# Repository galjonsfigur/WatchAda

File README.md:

# Ada-powereded digital watch

This repository contains Schematics, KiCad design files and software for Ada-powereded digital watch.
It uses wonderful work of [msp430-ada project](https://sourceforge.net/projects/msp430ada/) by Brian Drummond.
Software for this watch is a modification of original project and adds missing
features like automatic brightness, temperature reading and Easter Egg.

Revision 1 of the PCB was tested and following problems have been found:

- Incorrect footprint of CR2032 Battery holder
- THT Crystal footprint is too big and will be replaced with Epson MC-146 32kHz Crystal

Revision 2 fixed those problems and after about year of testing it haven't showed other flaws.
More photos and renders can be found in `photos` folder.

GCC compiler for building this project can be found in this repository. It was built on CentOS 6 x64 and should work with any modern 64-bit GNU/Linux distribution.
Docker image for it is still in progress as it requires exact same version of host GCC and patches from MSP430-Ada project.

## BOM and assembly instructions
Interactive BOM can be found [here](hardware/rev2/bom/ibom.html).

Remember to start with SMD components. Program the MSP430, put the display in place and
test it before soldering it to the board.

Case can be 3D printed with semi-transparent material or cut from thin PMMA.

The best way to program the microcontroller is to use [SOICBite](https://github.com/SimonMerrett/SOICbite) connected
to MSP430-G2 Launchpad. Pin layout can be found in the schematic and only TEST, RST, GND and 3V need to be used to program it.
After connecting the SOICBite, `make flash` command can be used. It uses `mspdebug` program and works only on GNU/Linux environment.
The firmware binary can be found in `firmware/obj` folder.

# License
GPL (Same as MSP430-Ada project)

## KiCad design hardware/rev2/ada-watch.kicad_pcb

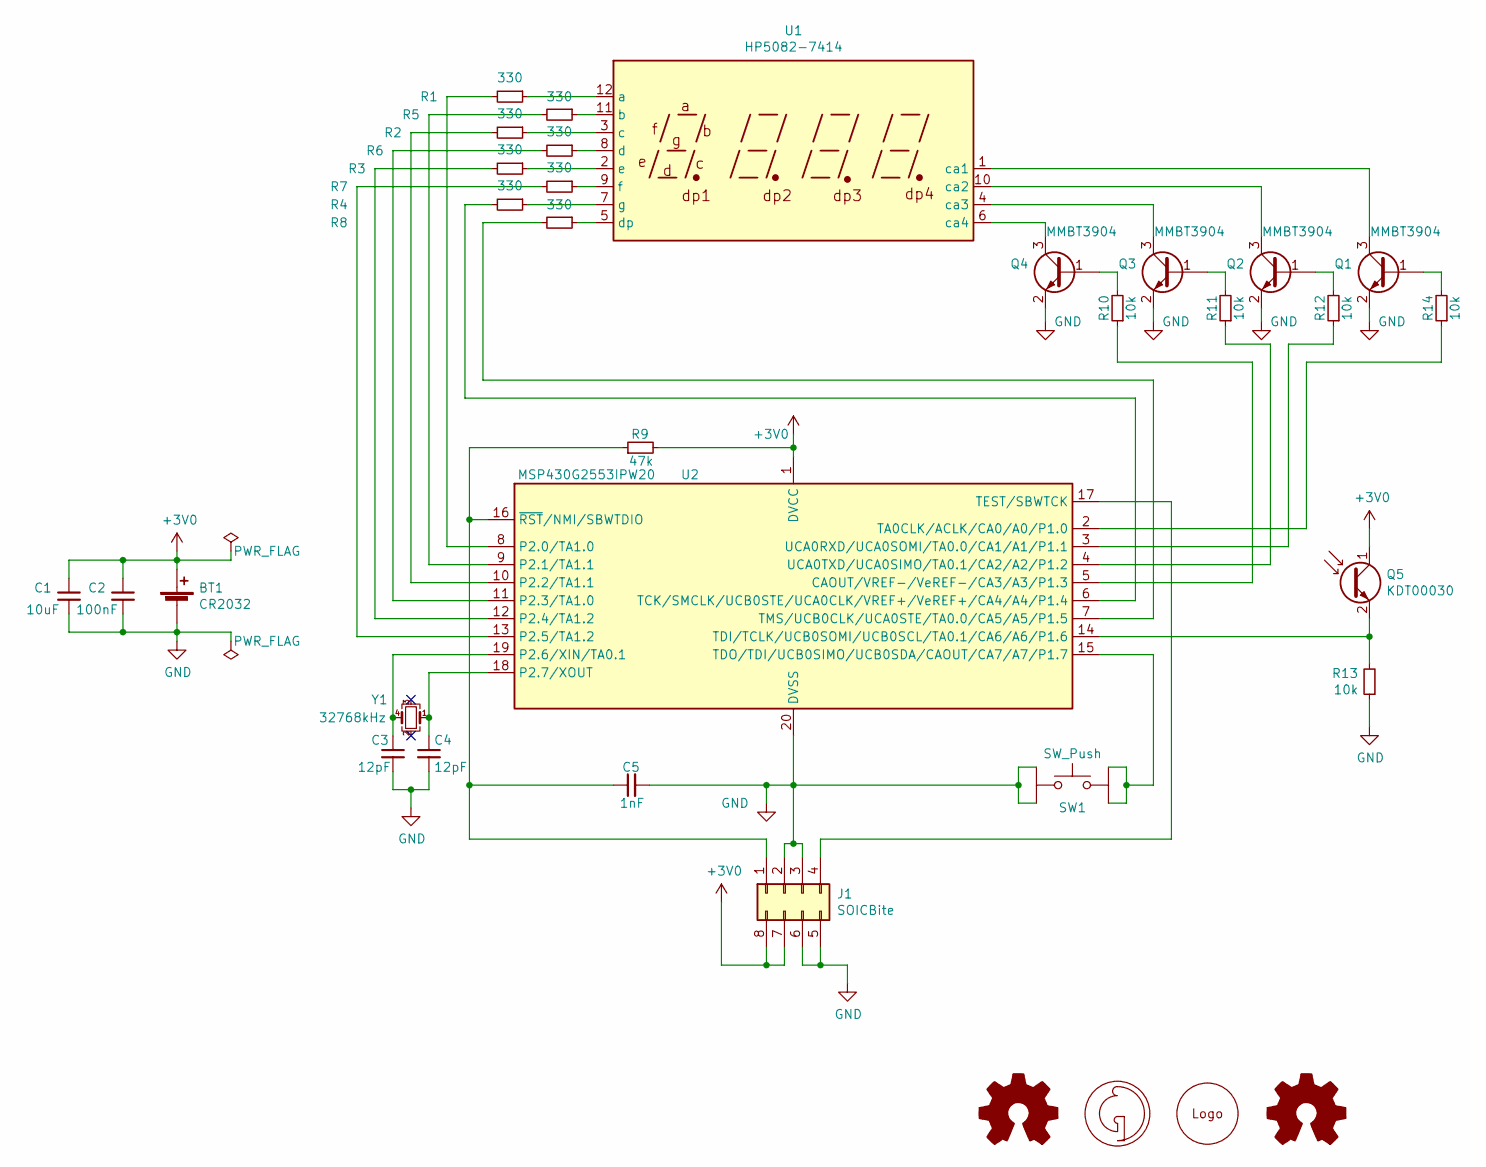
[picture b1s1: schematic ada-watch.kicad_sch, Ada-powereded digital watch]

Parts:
BT1: CR2032; BatteryHolder_Pinrex_780-72-00GF51_1x2032_customSilk
C1: 10uF; C_0805_2012Metric
C2: 100nF; C_0805_2012Metric
C3, C4: 12pF; C_0402_1005Metric
C5: 1nF; C_0402_1005Metric
J1: SOICBite; SOIC_clipProgSmall
LG1: Ada_Logo_Small
LG2: Galion_Logo; Galion_Logo_Small
LG3: Logo_Open_Hardware_Small; OSHW-Logo_5.7x6mm_SilkScreen
LG4: Logo_Designed_With_KiCad; KiCad-Logo_6mm_SilkScreen
Q1, Q2, Q3, Q4: MMBT3904; SOT-23
Q5: KDT00030; LED_0603_1608Metric
R1, R2, R3, R4, R5, R6, R7, R8: 330; R_0603_1608Metric_Pad1.05x0.95mm_HandSolder
R9: 47k; R_0603_1608Metric
R10, R11, R12, R13, R14: 10k; R_0603_1608Metric_Pad1.05x0.95mm_HandSolder
SW1: SW_Push; SKRPACE010
U1: HP5082-7414; DIP-12_W7.62mm_CustomPads_NoSilk
U2: MSP430G2553IPW20; TSSOP-20_4.4x6.5mm_P0.65mm
Y1: 32768kHz; Crystal_SMD_SeikoEpson_MC146-4Pin_6.7x1.5mm_HandSoldering

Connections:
+3V0: BT1.1 (+), C1.1, C2.1, J1.7, J1.8, Q5.1 (C), R9.2, U2.1 (DVCC)
GND: BT1.2 (-), C1.2, C2.2, C3.2, C4.2, C5.2, J1.2, J1.3, J1.5, J1.6, Q1.2 (E), Q2.2 (E), Q3.2 (E), Q4.2 (E), R13.1, SW1.3, SW1.4, U2.20 (DVSS)
unnamed: C3.1, U2.19 (P2.6/XIN/TA0.1), Y1.4
unnamed: C4.1, U2.18 (P2.7/XOUT), Y1.1
unnamed: C5.1, J1.1, R9.1, U2.16 (~RST~/NMI/SBWTDIO)
unnamed: J1.4, U2.17 (TEST/SBWTCK)
unnamed: Q1.1 (B), R14.2
unnamed: Q1.3 (C), U1.1 (ca1)
unnamed: Q2.1 (B), R12.2
unnamed: Q2.3 (C), U1.10 (ca2)
unnamed: Q3.1 (B), R11.2
unnamed: Q3.3 (C), U1.4 (ca3)
unnamed: Q4.1 (B), R10.2
unnamed: Q4.3 (C), U1.6 (ca4)
unnamed: Q5.2 (E), R13.2, U2.14 (TDI/TCLK/UCB0SOMI/UCB0SCL/TA0.1/CA6/A6/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)
unnamed: R1.1, U1.12 (a)
unnamed: R1.2, U2.8 (P2.0/TA1.0)
unnamed: R2.1, U1.3 (c)
unnamed: R2.2, U2.10 (P2.2/TA1.1)
unnamed: R3.1, U1.2 (e)
unnamed: R3.2, U2.12 (P2.4/TA1.2)
unnamed: R4.1, U1.7 (g)
unnamed: R4.2, U2.6 (TCK/SMCLK/UCB0STE/UCA0CLK/VREF+/VeREF+/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)
unnamed: R5.1, U1.11 (b)
unnamed: R5.2, U2.9 (P2.1/TA1.1)
unnamed: R6.1, U1.8 (d)
unnamed: R6.2, U2.11 (P2.3/TA1.0)
unnamed: R7.1, U1.9 (f)
unnamed: R7.2, U2.13 (P2.5/TA1.2)
unnamed: R8.1, U1.5 (dp)
unnamed: R8.2, U2.7 (TMS/UCB0CLK/UCA0STE/TA0.0/CA5/A5/P1.5)
unnamed: R10.1, U2.5 (CAOUT/VREF-/VeREF-/CA3/A3/P1.3)
unnamed: R11.1, U2.4 (UCA0TXD/UCA0SIMO/TA0.1/CA2/A2/P1.2)
unnamed: R12.1, U2.3 (UCA0RXD/UCA0SOMI/TA0.0/CA1/A1/P1.1)
unnamed: R14.1, U2.2 (TA0CLK/ACLK/CA0/A0/P1.0)
unnamed: SW1.1, SW1.2, U2.15 (TDO/TDI/UCB0SIMO/UCB0SDA/CAOUT/CA7/A7/P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)

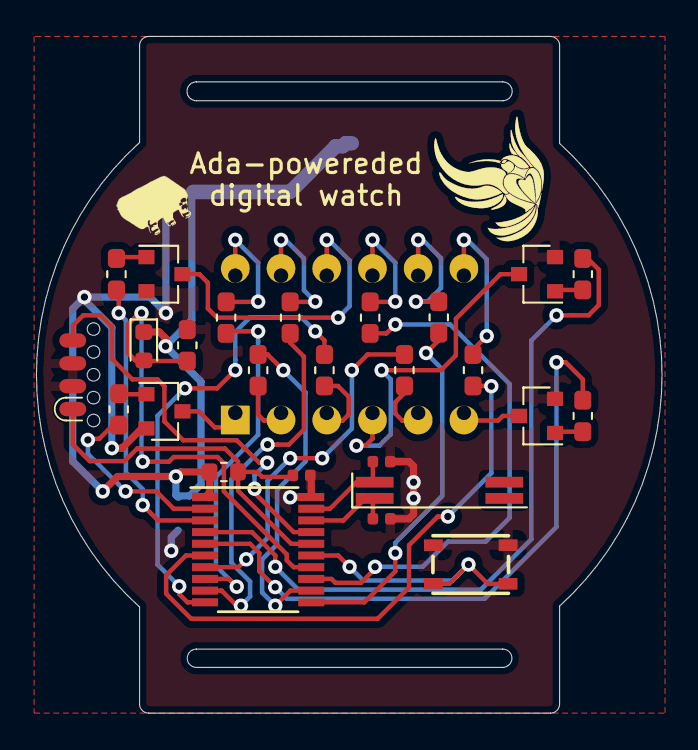
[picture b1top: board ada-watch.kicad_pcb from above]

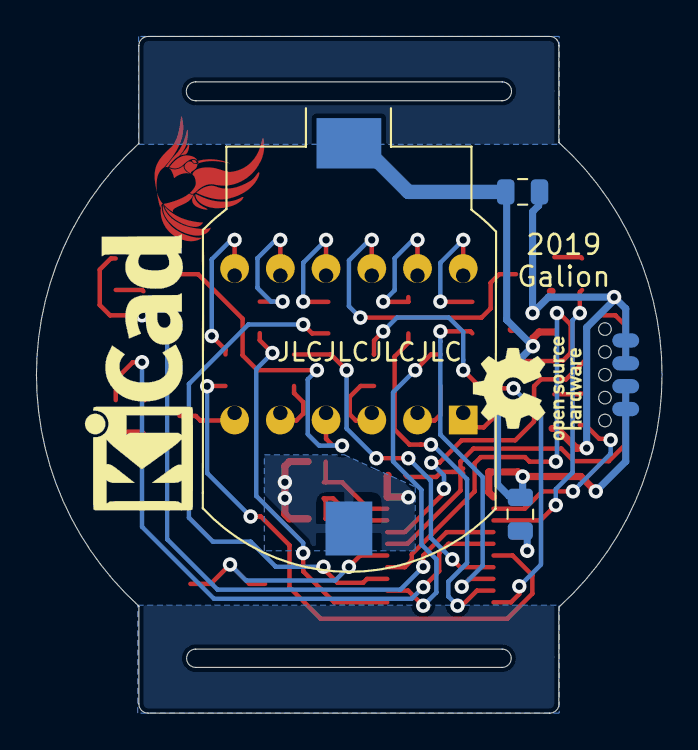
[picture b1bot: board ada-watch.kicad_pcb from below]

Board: 2 copper layers, 34.8 x 37.6 mm, 34 parts (5 on the bottom side), 36 nets.

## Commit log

2021-02-15 Add revision 2 of the PCB
2021-02-15 Add case files
2021-02-15 Version 2 of the software with easter egg and light/temp measurement
2021-03-25 Add .gitattributes to fix GitHub Statistics
2021-03-25 Add instructions on how to program watch
2021-03-25 Add more photos and move them to separate directory
